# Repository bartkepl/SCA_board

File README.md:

# SCA (Standalone Connector Adapter)
Standalone Connector Adapter for other 3U eurocards. Converts DIN41612 connector to USB, USB(UART converter), ETHERNET and RS485

---
## Status : WIP

- First revision of schematic and PCB is done. 
- Board for testing other boards and their software
  
---

## Features:
- 4x JST PH for USB, USB-UART, RS486 and RS232 
- 10/100/1000 Ethernet connector 
- 3U 6TE eurocard IEEE 1101.1-1998 format (128x30,1 mm)

## License and Contribution

[MIT License](/LICENSE)

Open to contributions in both software and hardware!

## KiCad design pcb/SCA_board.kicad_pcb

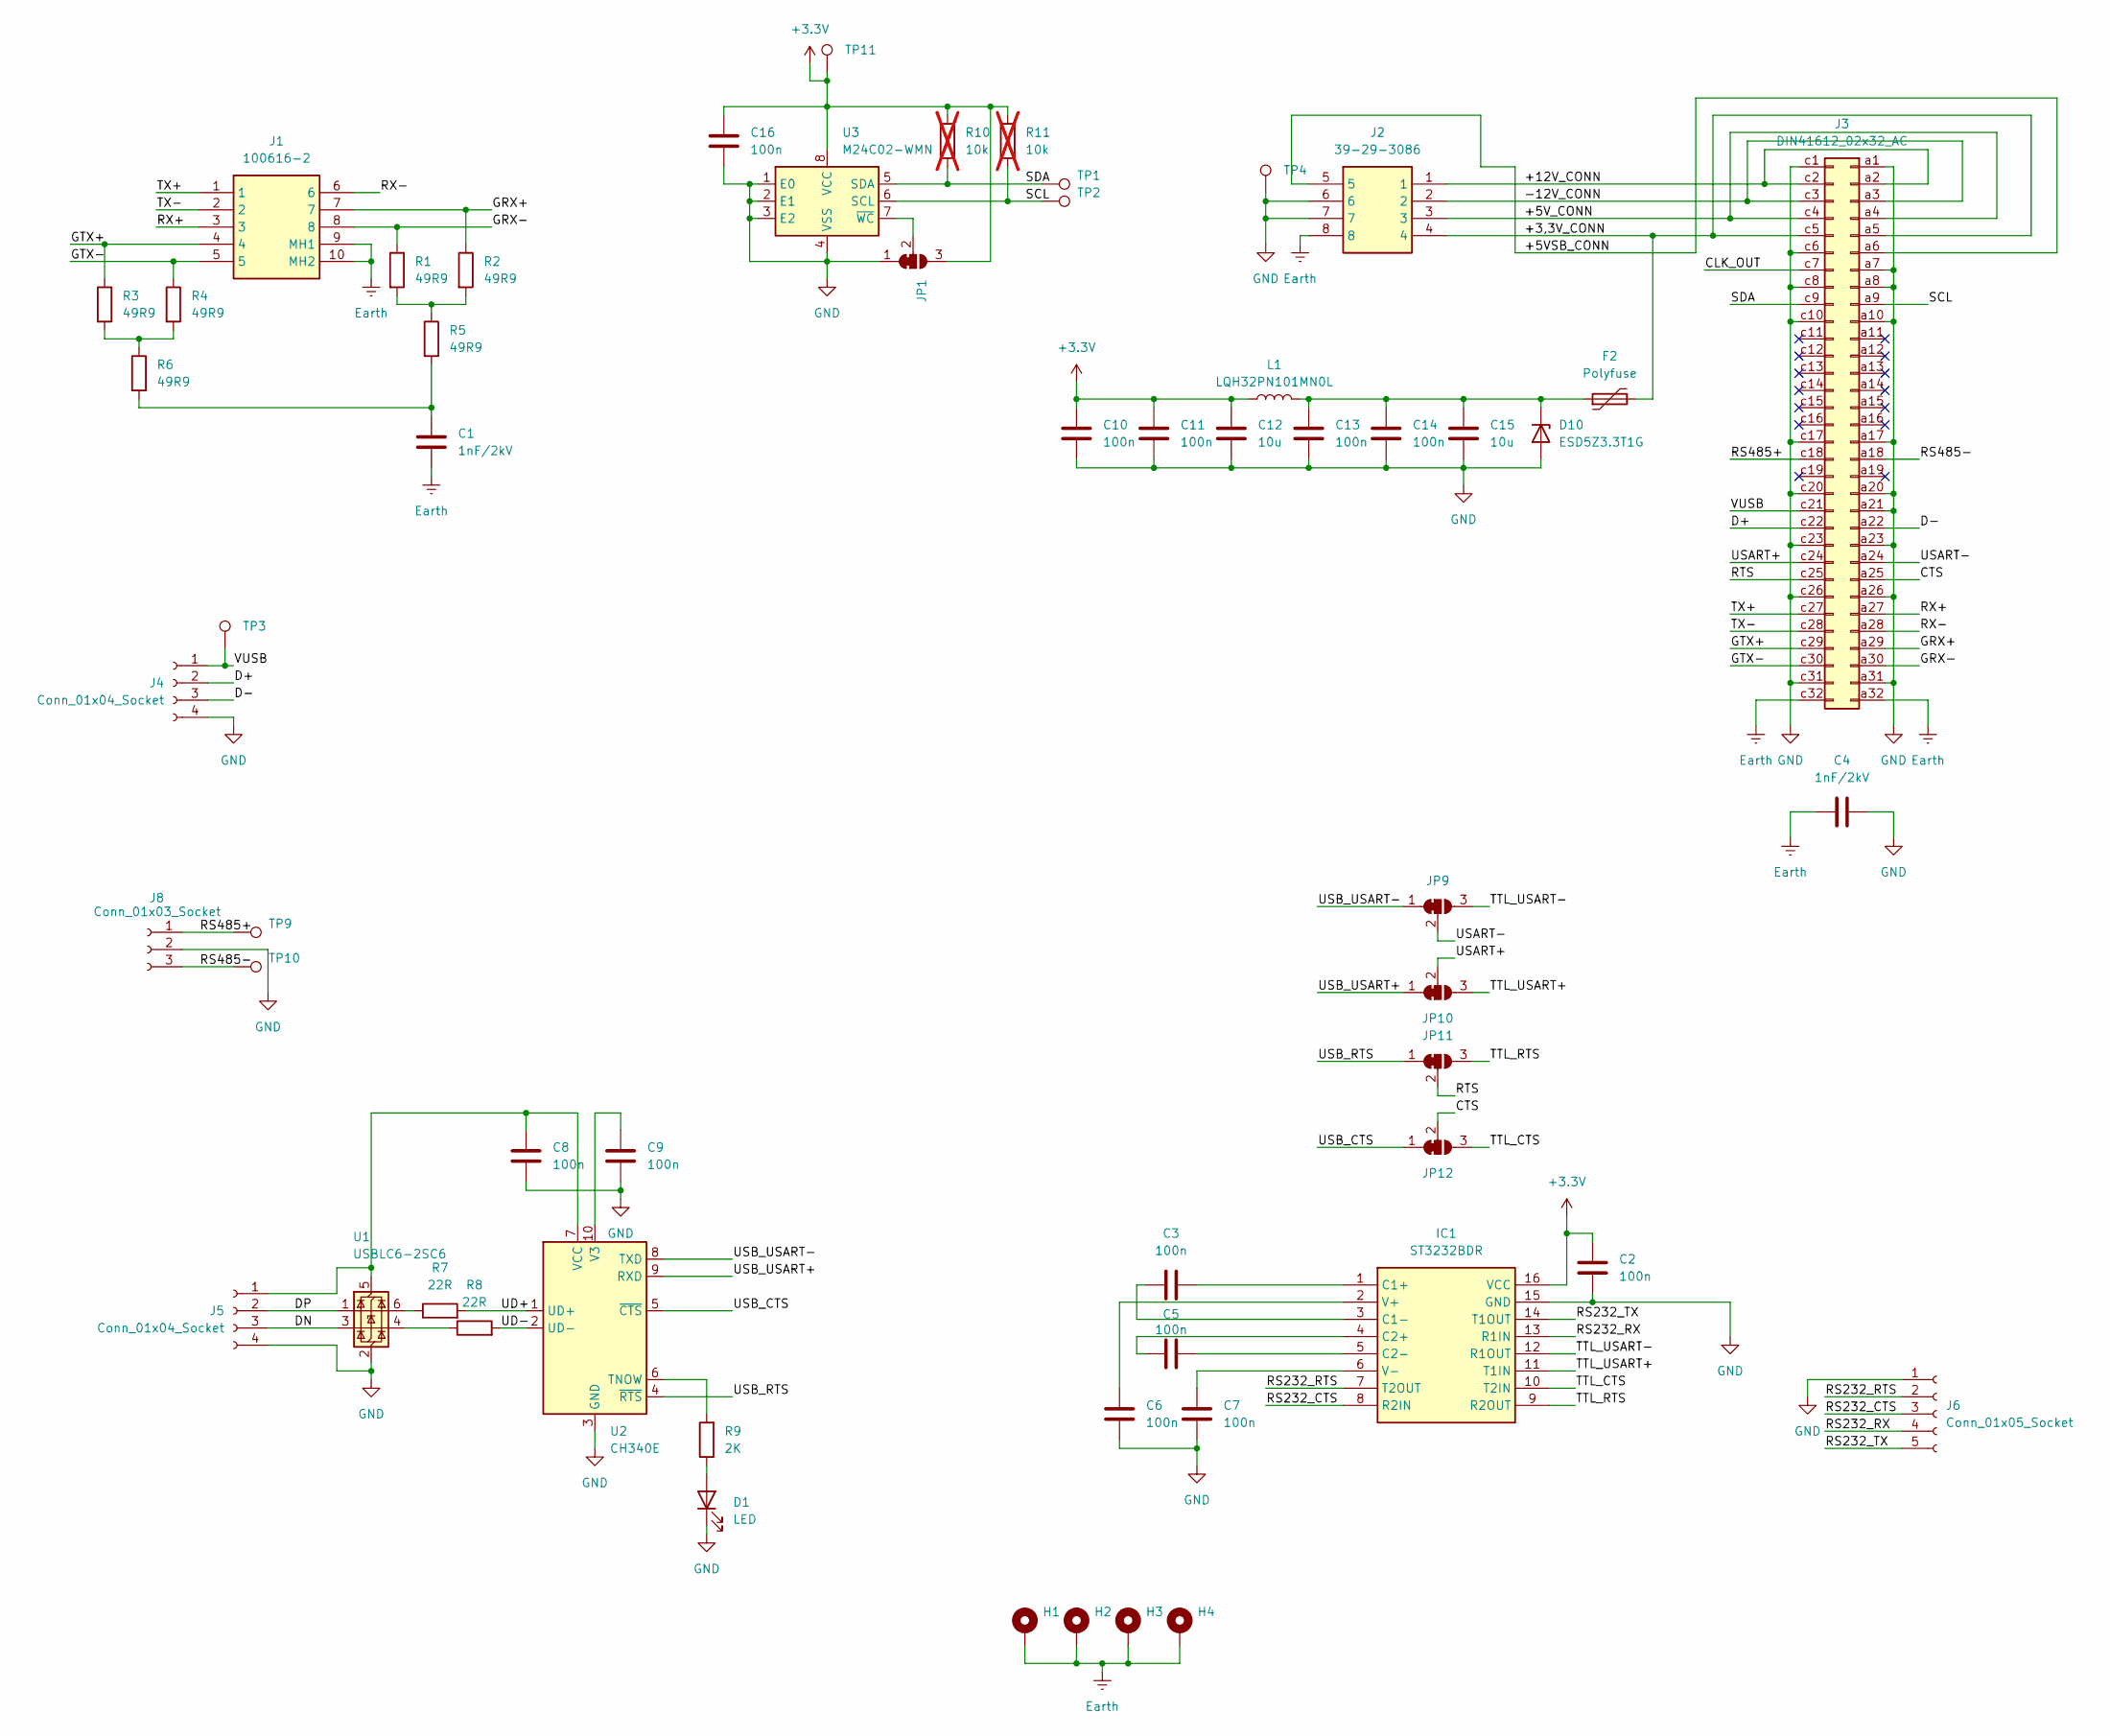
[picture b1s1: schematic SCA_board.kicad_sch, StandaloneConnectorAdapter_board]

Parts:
C1, C4: 1nF/2kV; C_1206_3216Metric_Pad1.33x1.80mm_HandSolder
C2, C3, C5, C6, C7, C8, C9, C10, C11, C13, C14, C16: 100n; C_0603_1608Metric_Pad1.08x0.95mm_HandSolder
C12, C15: 10u; C_1206_3216Metric_Pad1.33x1.80mm_HandSolder
D1: LED; LED_0603_1608Metric_Pad1.05x0.95mm_HandSolder
D10: ESD5Z3.3T1G; D_SOD-523
F2: Polyfuse; Fuse_1206_3216Metric_Pad1.42x1.75mm_HandSolder
H1, H2, H3, H4: MountingHole_Pad; MountingHole_2.7mm_M2.5_DIN965_Pad
IC1: ST3232BDR; SOIC127P600X175-16N; Manufacturer_Part_Number ST3232BDR
J1: 100616-2; 1006162; Manufacturer_Part_Number 100616-2
J2: 39-29-3086; Molex_Mini-Fit_Jr_5566-08A_2x04_P4.20mm_Vertical; Manufacturer_Part_Number 39-29-3086
J3: DIN41612_02x32_AC; DIN41612_C_2x32_Female_Vertical_THT
J4, J5: Conn_01x04_Socket; JST_PH_B4B-PH-K_1x04_P2.00mm_Vertical
J6: Conn_01x05_Socket; JST_PH_B5B-PH-K_1x05_P2.00mm_Vertical
J8: Conn_01x03_Socket; JST_PH_B3B-PH-K_1x03_P2.00mm_Vertical
JP1, JP9, JP10, JP11, JP12: SolderJumper_3_Bridged12; SolderJumper-3_P1.3mm_Bridged12_Pad1.0x1.5mm
L1: LQH32PN101MN0L; L_1210_3225Metric
R1, R2, R3, R4, R5, R6: 49R9; R_0603_1608Metric_Pad0.98x0.95mm_HandSolder
R7, R8: 22R; R_0402_1005Metric_Pad0.72x0.64mm_HandSolder
R9: 2K; R_0805_2012Metric_Pad1.20x1.40mm_HandSolder
R10, R11: 10k; R_0603_1608Metric_Pad0.98x0.95mm_HandSolder; not fitted
TP1, TP2, TP3, TP4, TP9, TP10, TP11: TestPoint; TestPoint_Pad_D1.0mm
U1: USBLC6-2SC6; SOT-23-6_Handsoldering
U2: CH340E; MSOP-10_3x3mm_P0.5mm
U3: M24C02-WMN; SOIC-8_3.9x4.9mm_P1.27mm

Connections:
+3.3V: C2.1, C10.1, C11.1, C12.1, C16.2, IC1.16 (VCC), JP1.3 (B), L1.1, R10.2, R11.2, TP11.1, U3.8 (VCC)
/+3,3V_CONN: F2.2, J2.4, J3.a5, J3.c5
/+5VSB_CONN: J2.5, J3.a6
/+5V_CONN: J2.3, J3.a4, J3.c4
/+12V_CONN: J2.1, J3.a2, J3.c2
/-12V_CONN: J2.2, J3.a3, J3.c3
/CLK_OUT: J3.c7
/CTS: J3.a25, JP12.2 (C)
/D+: J3.c22, J4.2
/D-: J3.a22, J4.3
/DN: J5.3, U1.3 (I/O2)
/DP: J5.2, U1.1 (I/O1)
/GRX+: J1.7, J3.a29, R2.1
/GRX-: J1.8, J3.a30, R1.1
/GTX+: J1.4, J3.c29, R3.1
/GTX-: J1.5, J3.c30, R4.1
/RS232_CTS: IC1.8 (R2IN), J6.3
/RS232_RTS: IC1.7 (T2OUT), J6.2
/RS232_RX: IC1.13 (R1IN), J6.4
/RS232_TX: IC1.14 (T1OUT), J6.5
/RS485+: J3.c18, J8.1, TP9.1
/RS485-: J3.a18, J8.3, TP10.1
/RTS: J3.c25, JP11.2 (C)
/RX+: J1.3, J3.a27
/RX-: J1.6, J3.a28
/SCL: J3.a9, R11.1, TP2.1, U3.6 (SCL)
/SDA: J3.c9, R10.1, TP1.1, U3.5 (SDA)
/TTL_CTS: IC1.10 (T2IN), JP12.3 (B)
/TTL_RTS: IC1.9 (R2OUT), JP11.3 (B)
/TTL_USART+: IC1.11 (T1IN), JP10.3 (B)
/TTL_USART-: IC1.12 (R1OUT), JP9.3 (B)
/TX+: J1.1, J3.c27
/TX-: J1.2, J3.c28
/UD+: R7.2, U2.1 (UD+)
/UD-: R8.2, U2.2 (UD-)
/USART+: J3.c24, JP10.2 (C)
/USART-: J3.a24, JP9.2 (C)
/USB_CTS: JP12.1 (A), U2.5 (~CTS)
/USB_RTS: JP11.1 (A), U2.4 (~RTS)
/USB_USART+: JP10.1 (A), U2.9 (RXD)
/USB_USART-: JP9.1 (A), U2.8 (TXD)
/VUSB: J3.c21, J4.1, TP3.1
Earth: C1.2, C4.1, H1.1, H2.1, H3.1, H4.1, J1.9 (MH1), J1.10 (MH2), J2.8, J3.a32, J3.c32
GND: C2.2, C4.2, C6.1, C7.1, C8.1, C9.1, C10.2, C11.2, C12.2, C13.2, C14.2, C15.2, C16.1, D1.1 (K), D10.2 (A), IC1.15 (GND), J2.6, J2.7, J3.a1, J3.a7, J3.a8, J3.a10, J3.a17, J3.a20, J3.a21, J3.a23, J3.a26, J3.a31, J3.c1, J3.c6, J3.c8, J3.c10, J3.c17, J3.c20, J3.c23, J3.c26, J3.c31, J4.4, J5.4, J6.1, J8.2, JP1.1 (A), TP4.1, U1.2 (GND), U2.3 (GND), U3.1 (E0), U3.2 (E1), U3.3 (E2), U3.4 (VSS)
unnamed: C1.1, R5.2, R6.2
unnamed: D1.2 (A), R9.1
unnamed: C13.1, C14.1, C15.1, D10.1 (K), F2.1, L1.2
unnamed: C3.2, IC1.1 (C1+)
unnamed: C3.1, IC1.3 (C1-)
unnamed: C5.1, IC1.4 (C2+)
unnamed: C5.2, IC1.5 (C2-)
unnamed: C6.2, IC1.2 (V+)
unnamed: C7.2, IC1.6 (V-)
unnamed: C8.2, J5.1, U1.5 (VBUS), U2.7 (VCC)
unnamed: JP1.2 (C), U3.7 (~WC)
unnamed: R1.2, R2.2, R5.1
unnamed: R3.2, R4.2, R6.1
unnamed: R7.1, U1.6 (I/O1)
unnamed: R8.1, U1.4 (I/O2)
unnamed: R9.2, U2.6 (TNOW)
unnamed: C9.2, U2.10 (V3)

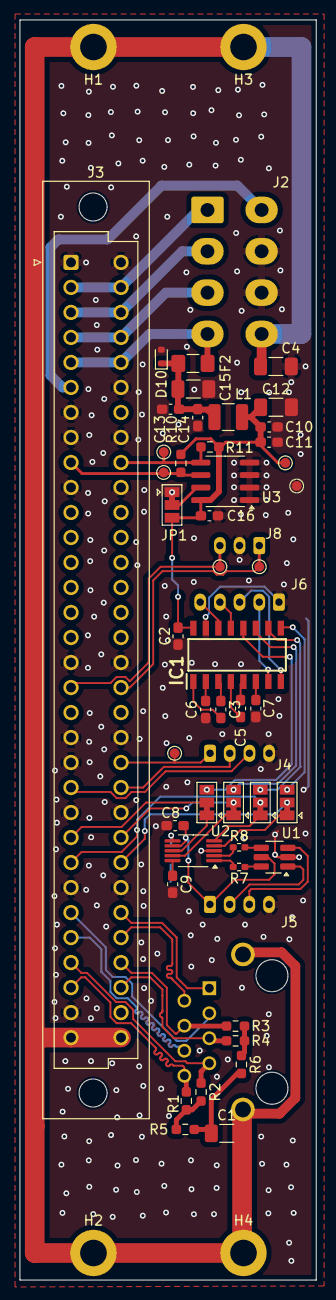
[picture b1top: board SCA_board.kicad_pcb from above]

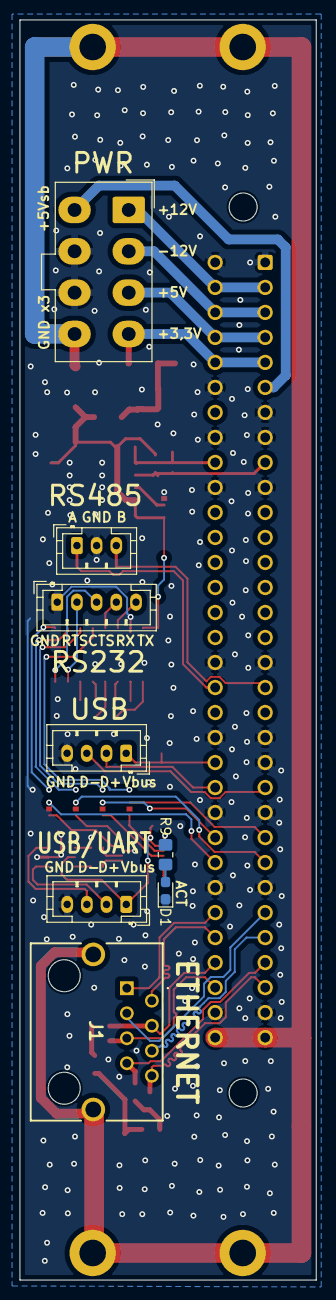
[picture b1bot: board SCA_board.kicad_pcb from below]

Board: 2 copper layers, 30.1 x 128.0 mm, 58 parts (8 on the bottom side), 60 nets.

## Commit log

2026-02-12 First board revision for testing others boards
2026-02-12 Updated README and file rename
2026-02-14 Added i2c config eeprom and testpoints
2026-02-21 Changed file organization
2026-02-21 Connector and layout change
2026-02-21 Cleaning
2026-02-21 Added stitching
2026-02-21 Repaired stitching
2026-02-21 First production
2026-03-10 Repaired image
